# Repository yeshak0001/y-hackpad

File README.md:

# y-pad
y-pad is a 4 key macropad with a rotary encoder and 2 LEDs.
It's been designed via Onshape, KiCAD, and kmk via Mu

## Features
- 4x MX-style mechanical switches
- 1x EC11 rotary encoder with push-click
- 2x SK6812 MINI RGB LEDs
- Seeed XIAO RP2040 microcontroller
- 3D printed two-piece case with heatset inserts
- Fully open source firmware via KMK

## Overall Design

## CAD

The case is a two-piece 3D printed design — a top plate with cutouts for the switches, encoder, and USB passthrough, and a hollow bottom shell. The PCB sits between them, secured with M3 heatset inserts and screws.

## Schematic

## PCB

## BOM

| Part | Quantity |
|------|----------|
| Seeed XIAO RP2040 | 1 |
| MX-style mechanical switches | 4 |
| EC11 rotary encoder | 1 |
| SK6812 MINI LEDs | 2 |
| M3x16mm screws | 4 |
| M3x5mmx4mm heatset inserts | 4 |
| Custom PCB | 1 |
| 3D printed top plate | 1 |
| 3D printed bottom shell | 1 |

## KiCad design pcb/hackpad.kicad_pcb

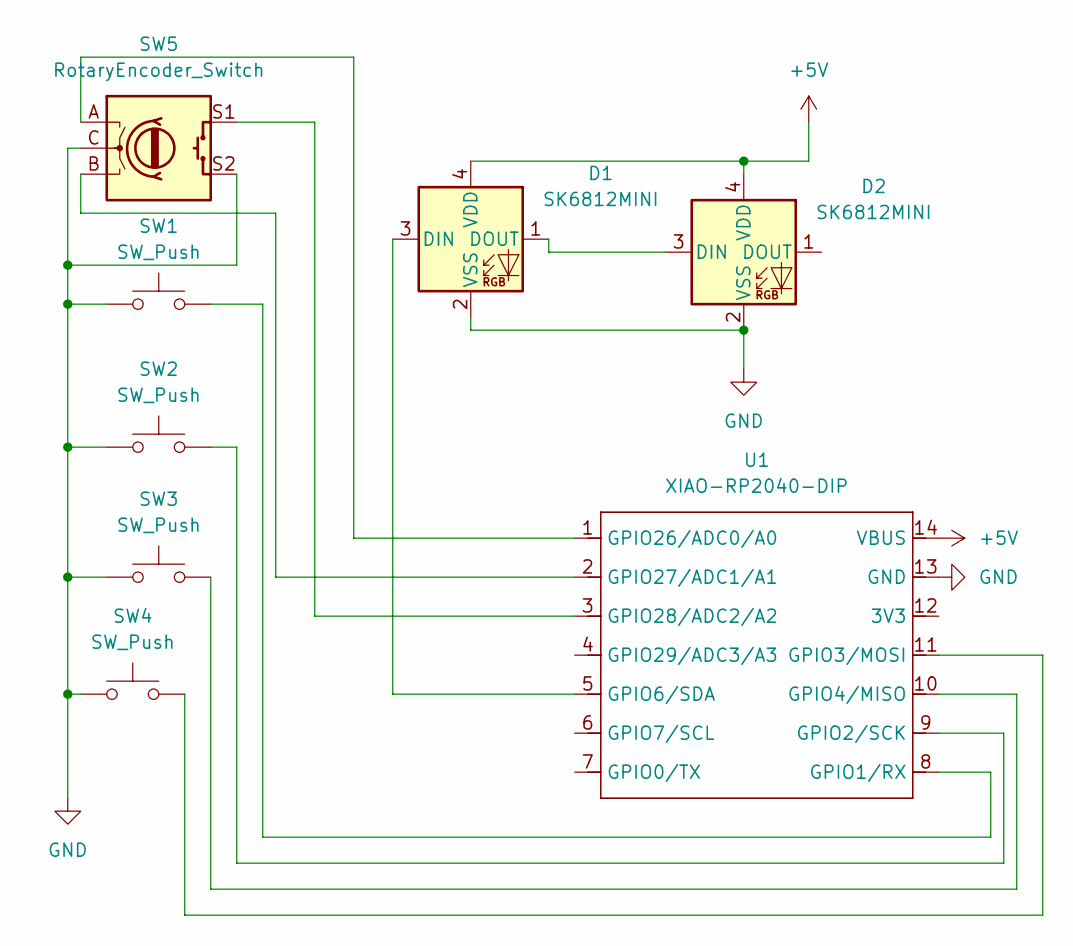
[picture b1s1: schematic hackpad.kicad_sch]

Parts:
D1, D2: SK6812MINI; LED_SK6812MINI_PLCC4_3.5x3.5mm_P1.75mm
SW1, SW2, SW3, SW4: SW_Push; SW_Cherry_MX_1.00u_PCB
SW5: RotaryEncoder_Switch; RotaryEncoder_Alps_EC11E-Switch_Vertical_H20mm
U1: XIAO-RP2040-DIP

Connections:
+5V: D1.4 (VDD), D2.4 (VDD), U1.14 (VBUS)
GND: D1.2 (VSS), D2.2 (VSS), SW1.1, SW2.1, SW3.1, SW4.1, SW5.C, SW5.S2, U1.13 (GND)
unnamed: D1.3 (DIN), U1.5 (GPIO6/SDA)
unnamed: D1.1 (DOUT), D2.3 (DIN)
unnamed: SW1.2, U1.8 (GPIO1/RX)
unnamed: SW2.2, U1.9 (GPIO2/SCK)
unnamed: SW4.2, U1.11 (GPIO3/MOSI)
unnamed: SW3.2, U1.10 (GPIO4/MISO)
unnamed: SW5.A, U1.1 (GPIO26/ADC0/A0)
unnamed: SW5.B, U1.2 (GPIO27/ADC1/A1)
unnamed: SW5.S1, U1.3 (GPIO28/ADC2/A2)

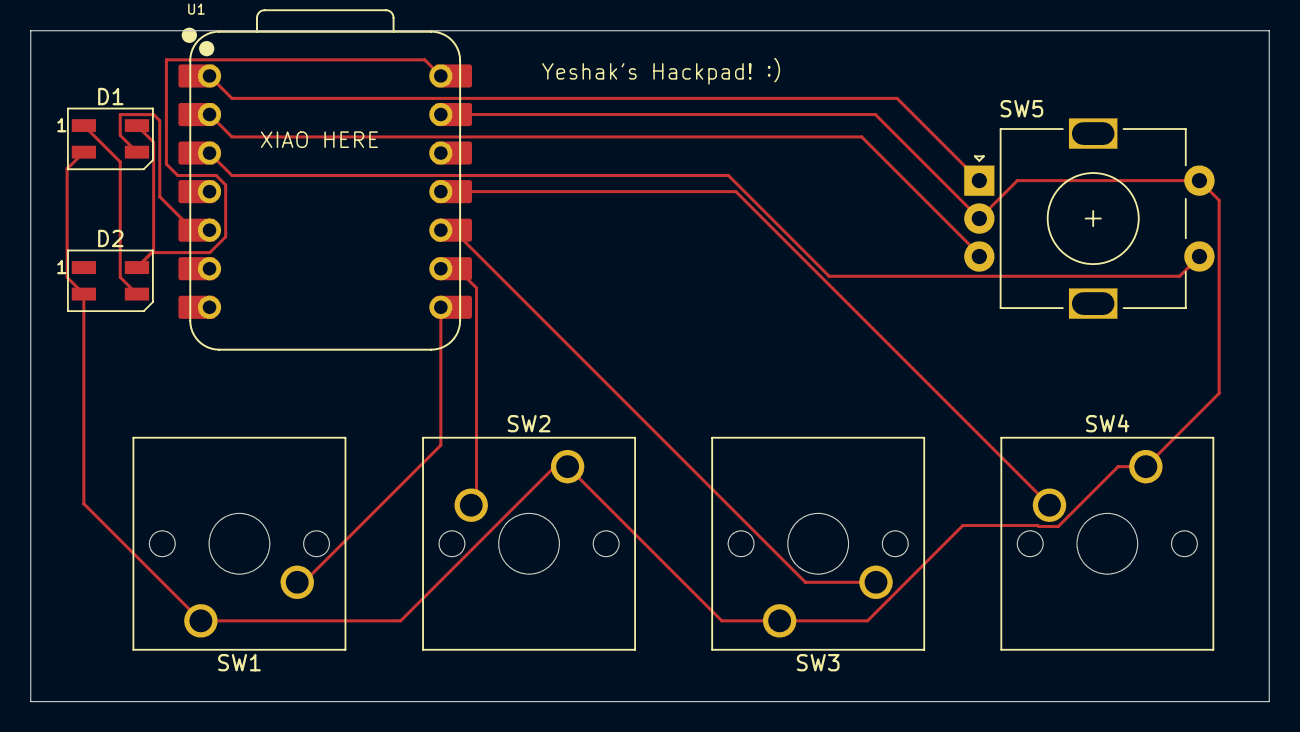
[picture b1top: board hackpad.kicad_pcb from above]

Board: 2 copper layers, 81.6 x 44.2 mm, 8 parts (0 on the bottom side), 11 nets.

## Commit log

2025-12-31 Working on README.md
2026-03-29 Upload cad
2026-03-29 Rename assembled macropad.step to cad/assembled macropad.step
2026-03-29 Rename bottom.step to cad/bottom.step
2026-03-29 Rename top.step to cad/top.step
2026-03-29 Create hello
2026-03-29 Rename bottom.step to bottom.step
2026-03-29 Rename top.step to top.step
2026-03-29 Rename case_exploded.png.png to case_exploded.png
2026-03-29 Rename hackpad_overall.png.png to hackpad_overall.png
2026-03-29 Rename pcb.png.png to pcb.png
2026-03-29 Rename schematic.png.png to schematic.png
